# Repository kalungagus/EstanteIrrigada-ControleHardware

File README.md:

# EstanteIrrigada-ControleHardware

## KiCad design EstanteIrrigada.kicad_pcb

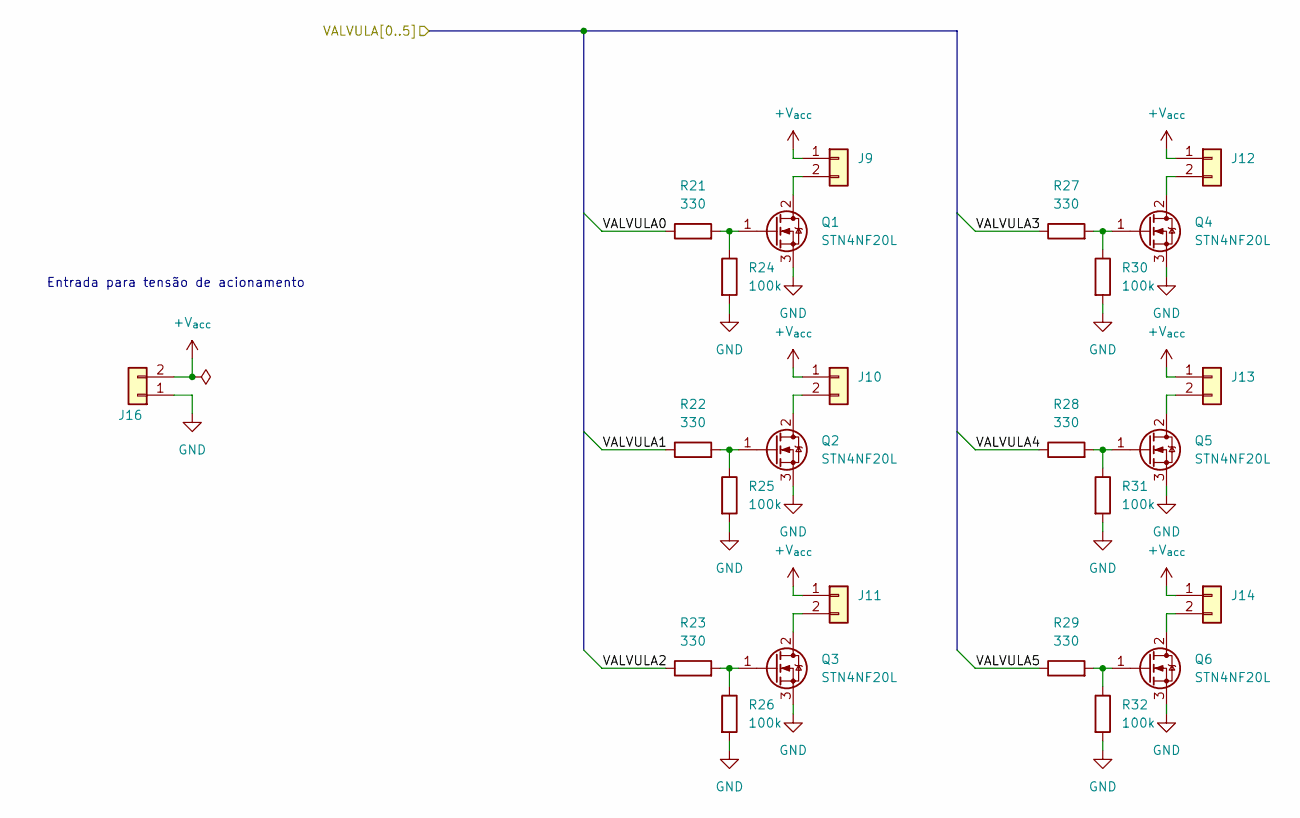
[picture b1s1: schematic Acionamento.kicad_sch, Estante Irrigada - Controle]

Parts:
J9, J10, J11, J12, J13, J14: Conn_01x02; PinHeader_1x02_P2.54mm_Vertical
J16: Conn_01x02; TerminalBlock_bornier-2_P5.08mm
Q1, Q2, Q3, Q4, Q5, Q6: STN4NF20L; SOT-223-3_TabPin2
R21, R22, R23, R27, R28, R29: 330; R_0805_2012Metric_Pad1.20x1.40mm_HandSolder
R24, R25, R26, R30, R31, R32: 100k; R_0805_2012Metric_Pad1.20x1.40mm_HandSolder

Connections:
+V_{acc}: J9.1, J10.1, J11.1, J12.1, J13.1, J14.1, J16.2
/Acionamento/VALVULA0: R21.1; also elsewhere on the board
/Acionamento/VALVULA1: R22.1; also elsewhere on the board
/Acionamento/VALVULA2: R23.1; also elsewhere on the board
/Acionamento/VALVULA3: R27.1; also elsewhere on the board
/Acionamento/VALVULA4: R28.1; also elsewhere on the board
/Acionamento/VALVULA5: R29.1; also elsewhere on the board
GND: J16.1, Q1.3 (S), Q2.3 (S), Q3.3 (S), Q4.3 (S), Q5.3 (S), Q6.3 (S), R24.2, R25.2, R26.2, R30.2, R31.2, R32.2; also elsewhere on the board
unnamed: J9.2, Q1.2 (D)
unnamed: J10.2, Q2.2 (D)
unnamed: J11.2, Q3.2 (D)
unnamed: J12.2, Q4.2 (D)
unnamed: J13.2, Q5.2 (D)
unnamed: J14.2, Q6.2 (D)
unnamed: Q1.1 (G), R21.2, R24.1
unnamed: Q2.1 (G), R22.2, R25.1
unnamed: Q3.1 (G), R23.2, R26.1
unnamed: Q4.1 (G), R27.2, R30.1
unnamed: Q5.1 (G), R28.2, R31.1
unnamed: Q6.1 (G), R29.2, R32.1

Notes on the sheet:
Entrada para tensão de acionamento

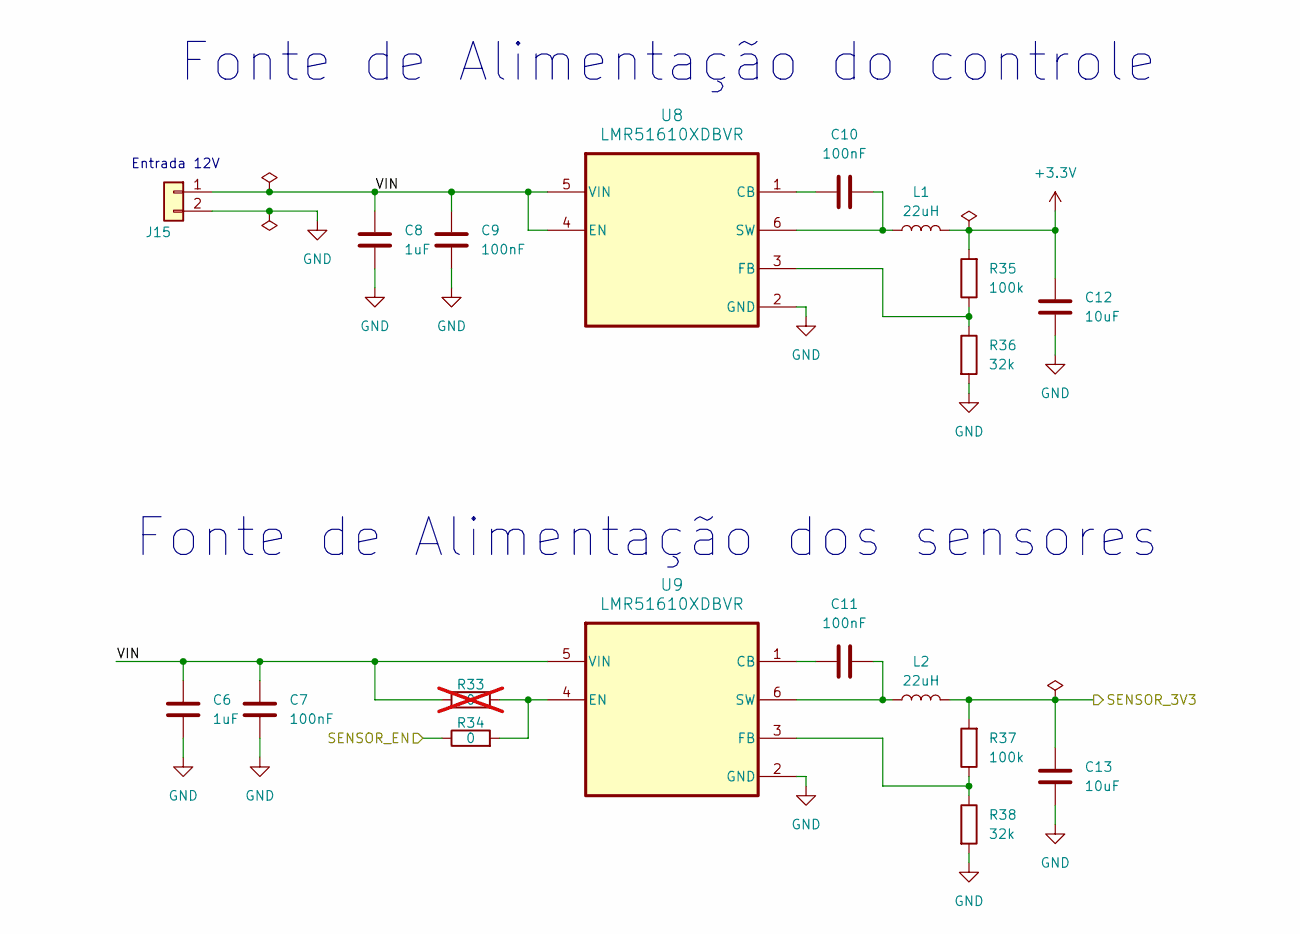
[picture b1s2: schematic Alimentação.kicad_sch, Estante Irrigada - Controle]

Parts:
C6, C8: 1uF; C_0805_2012Metric_Pad1.18x1.45mm_HandSolder
C7, C9, C10, C11: 100nF; C_0805_2012Metric_Pad1.18x1.45mm_HandSolder
C12, C13: 10uF; C_0805_2012Metric_Pad1.18x1.45mm_HandSolder
J15: Conn_01x02; TerminalBlock_bornier-2_P5.08mm
L1, L2: 22uH; L_7.3x7.3_H3.5
R33: 0; R_0805_2012Metric_Pad1.20x1.40mm_HandSolder; not fitted
R34: 0; R_0805_2012Metric_Pad1.20x1.40mm_HandSolder
R35, R37: 100k; R_0805_2012Metric_Pad1.20x1.40mm_HandSolder
R36, R38: 32k; R_0805_2012Metric_Pad1.20x1.40mm_HandSolder
U8, U9: LMR51610XDBVR; DBV0006A-IPC_A

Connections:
+3.3V: C12.1, L1.2, R35.2; also elsewhere on the board
/Alimentação/SENSOR_3V3: C13.1, L2.2, R37.2; also elsewhere on the board
/Alimentação/SENSOR_EN: R34.1; also elsewhere on the board
/Alimentação/VIN: C6.1, C7.1, C8.1, C9.1, J15.1, R33.1, U8.4 (EN), U8.5 (VIN), U9.5 (VIN)
GND: C6.2, C7.2, C8.2, C9.2, C12.2, C13.2, J15.2, R36.2, R38.2, U8.2 (GND), U9.2 (GND); also elsewhere on the board
unnamed: C10.1, U8.1 (CB)
unnamed: R35.1, R36.1, U8.3 (FB)
unnamed: C10.2, L1.1, U8.6 (SW)
unnamed: C11.1, U9.1 (CB)
unnamed: R33.2, R34.2, U9.4 (EN)
unnamed: R37.1, R38.1, U9.3 (FB)
unnamed: C11.2, L2.1, U9.6 (SW)

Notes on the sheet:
Entrada 12V
Fonte de Alimentação dos sensores
Fonte de Alimentação do controle

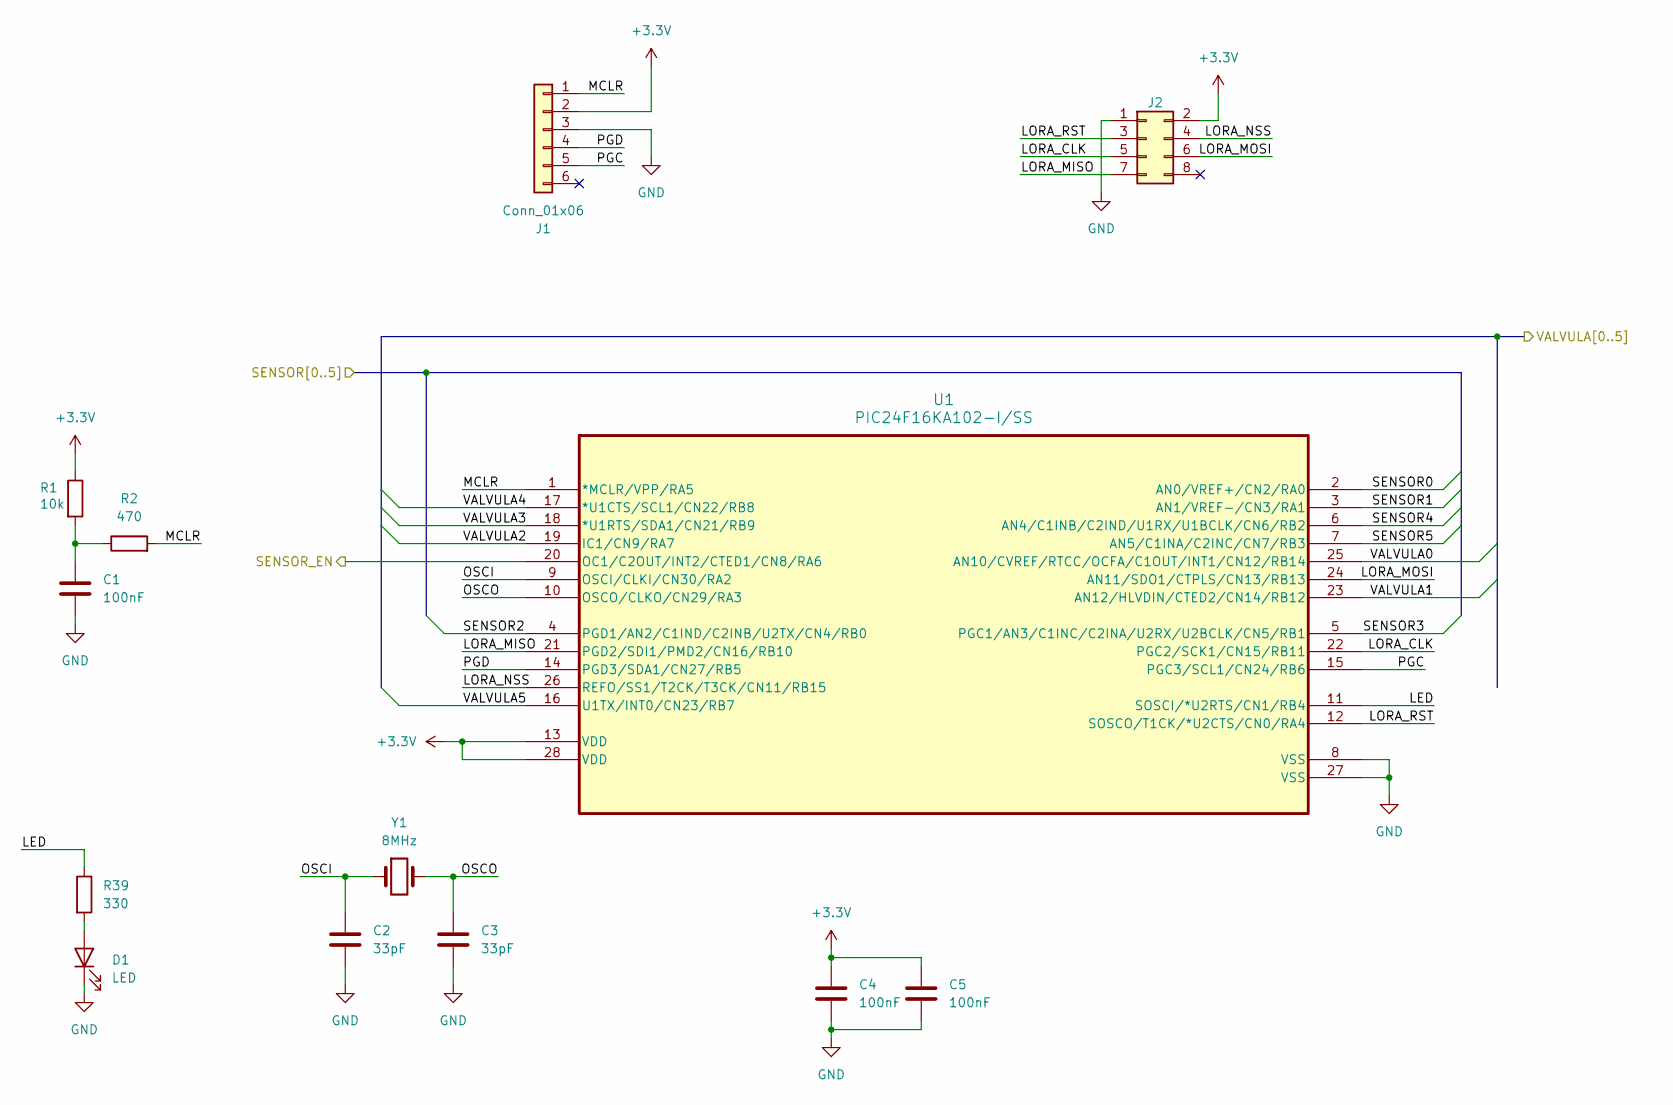
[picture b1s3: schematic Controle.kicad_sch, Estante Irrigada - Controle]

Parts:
C1, C4, C5: 100nF; C_0805_2012Metric_Pad1.18x1.45mm_HandSolder
C2, C3: 33pF; C_0805_2012Metric_Pad1.18x1.45mm_HandSolder
D1: LED; LED_0805_2012Metric_Pad1.15x1.40mm_HandSolder
J1: Conn_01x06; PinHeader_1x06_P2.54mm_Vertical
J2: Conn_02x04_Odd_Even; PinHeader_2x04_P2.54mm_Vertical
R1: 10k; R_0805_2012Metric_Pad1.20x1.40mm_HandSolder
R2: 470; R_0805_2012Metric_Pad1.20x1.40mm_HandSolder
R39: 330; R_0805_2012Metric_Pad1.20x1.40mm_HandSolder
U1: PIC24F16KA102-I/SS; SOP65P780X200-28N
Y1: 8MHz; HC-49&slash_US_11P4X3P8_IQD

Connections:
+3.3V: C4.1, C5.1, J1.2, J2.2, R1.1, U1.13 (VDD), U1.28 (VDD); also elsewhere on the board
/Acionamento/VALVULA0: U1.25 (AN10/CVREF/RTCC/OCFA/C1OUT/INT1/CN12/RB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); also elsewhere on the board
/Acionamento/VALVULA1: U1.23 (AN12/HLVDIN/CTED2/CN14/RB12); also elsewhere on the board
/Acionamento/VALVULA2: U1.19 (IC1/CN9/RA7); also elsewhere on the board
/Acionamento/VALVULA3: U1.18 (*U1RTS/SDA1/CN21/RB9); also elsewhere on the board
/Acionamento/VALVULA4: U1.17 (*U1CTS/SCL1/CN22/RB8); also elsewhere on the board
/Acionamento/VALVULA5: U1.16 (U1TX/INT0/CN23/RB7); also elsewhere on the board
/Alimentação/SENSOR_EN: U1.20 (OC1/C2OUT/INT2/CTED1/CN8/RA6); also elsewhere on the board
/Controle/LED: R39.1, U1.11 (SOSCI/*U2RTS/CN1/RB4)
/Controle/LORA_CLK: J2.5, U1.22 (PGC2/SCK1/CN15/RB11)
/Controle/LORA_MISO: J2.7, U1.21 (PGD2/SDI1/PMD2/CN16/RB10)
/Controle/LORA_MOSI: J2.6, U1.24 (AN11/SDO1/CTPLS/CN13/RB13)
/Controle/LORA_NSS: J2.4, U1.26 (REFO/SS1/T2CK/T3CK/CN11/RB15)
/Controle/LORA_RST: J2.3, U1.12 (SOSCO/T1CK/*U2CTS/CN0/RA4)
/Controle/MCLR: J1.1, R2.2, U1.1 (*MCLR/VPP/RA5)
/Controle/OSCI: C2.1, U1.9 (OSCI/CLKI/CN30/RA2), Y1.1
/Controle/OSCO: C3.1, U1.10 (OSCO/CLKO/CN29/RA3), Y1.2
/Controle/PGC: J1.5, U1.15 (PGC3/SCL1/CN24/RB6)
/Controle/PGD: J1.4, U1.14 (PGD3/SDA1/CN27/RB5)
/Controle/SENSOR0: U1.2 (AN0/VREF+/CN2/RA0); also elsewhere on the board
/Controle/SENSOR1: U1.3 (AN1/VREF-/CN3/RA1); also elsewhere on the board
/Controle/SENSOR2: U1.4 (PGD1/AN2/C1IND/C2INB/U2TX/CN4/RB0); also elsewhere on the board
/Controle/SENSOR3: U1.5 (PGC1/AN3/C1INC/C2INA/U2RX/U2BCLK/CN5/RB1); also elsewhere on the board
/Controle/SENSOR4: U1.6 (AN4/C1INB/C2IND/U1RX/U1BCLK/CN6/RB2); also elsewhere on the board
/Controle/SENSOR5: U1.7 (AN5/C1INA/C2INC/CN7/RB3); also elsewhere on the board
GND: C1.2, C2.2, C3.2, C4.2, C5.2, D1.1 (K), J1.3, J2.1, U1.8 (VSS), U1.27 (VSS); also elsewhere on the board
unnamed: C1.1, R1.2, R2.1
unnamed: D1.2 (A), R39.2

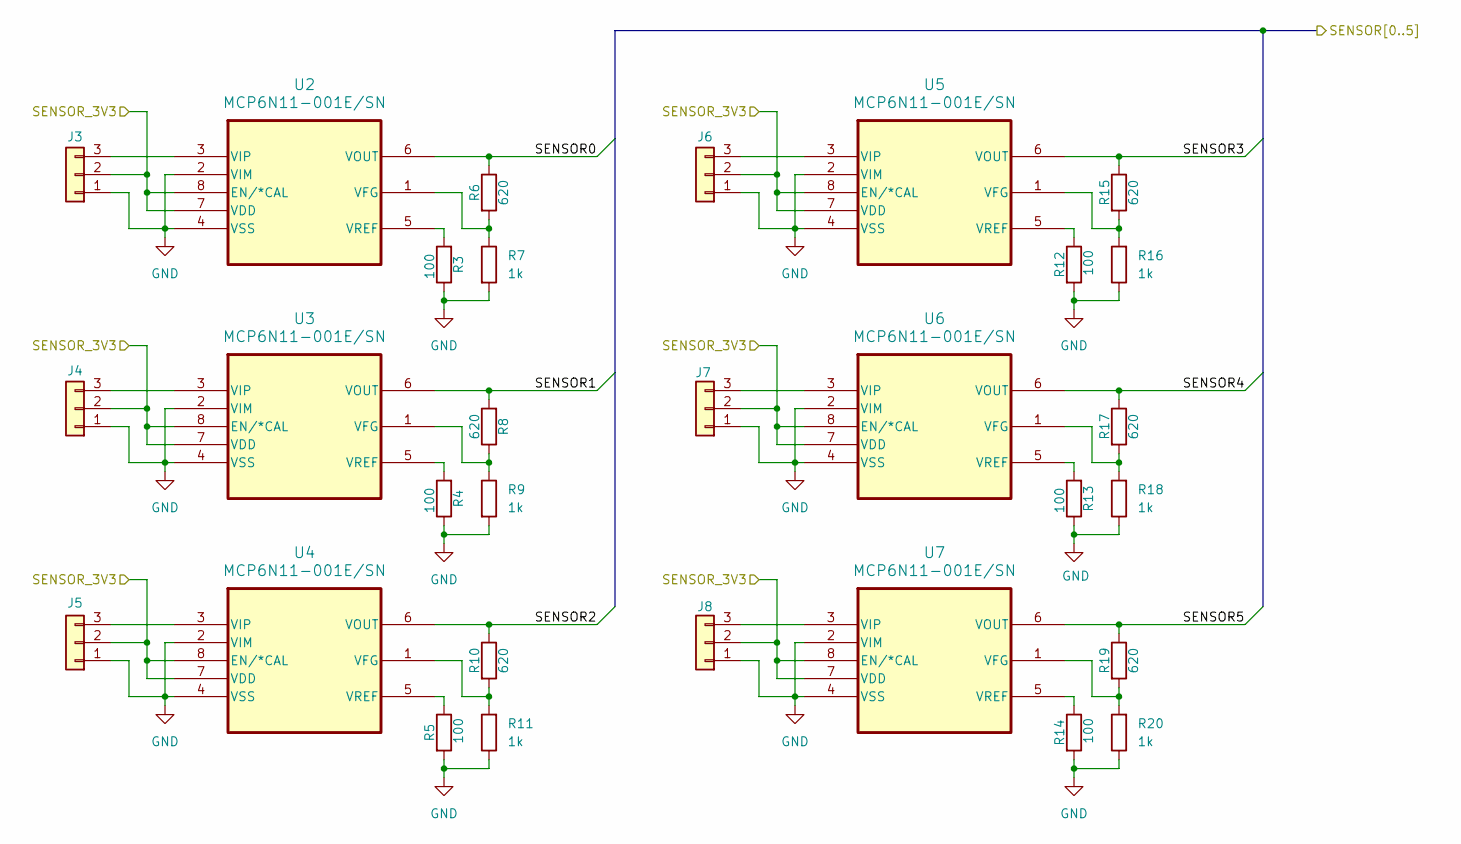
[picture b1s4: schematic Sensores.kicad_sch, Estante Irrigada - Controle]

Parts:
J3, J4, J5, J6, J7, J8: Conn_01x03; PinHeader_1x03_P2.54mm_Vertical
R3, R4, R5, R12, R13, R14: 100; R_0805_2012Metric_Pad1.20x1.40mm_HandSolder
R6, R8, R10, R15, R17, R19: 620; R_0805_2012Metric_Pad1.20x1.40mm_HandSolder
R7, R9, R11, R16, R18, R20: 1k; R_0805_2012Metric_Pad1.20x1.40mm_HandSolder
U2, U3, U4, U5, U6, U7: MCP6N11-001E/SN; SOIC8-N_MC_MCH

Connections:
/Alimentação/SENSOR_3V3: J3.2, J4.2, J5.2, J6.2, J7.2, J8.2, U2.7 (VDD), U2.8 (EN/*CAL), U3.7 (VDD), U3.8 (EN/*CAL), U4.7 (VDD), U4.8 (EN/*CAL), U5.7 (VDD), U5.8 (EN/*CAL), U6.7 (VDD), U6.8 (EN/*CAL), U7.7 (VDD), U7.8 (EN/*CAL); also elsewhere on the board
/Controle/SENSOR0: R6.1, U2.6 (VOUT); also elsewhere on the board
/Controle/SENSOR1: R8.2, U3.6 (VOUT); also elsewhere on the board
/Controle/SENSOR2: R10.1, U4.6 (VOUT); also elsewhere on the board
/Controle/SENSOR3: R15.1, U5.6 (VOUT); also elsewhere on the board
/Controle/SENSOR4: R17.1, U6.6 (VOUT); also elsewhere on the board
/Controle/SENSOR5: R19.1, U7.6 (VOUT); also elsewhere on the board
GND: J3.1, J4.1, J5.1, J6.1, J7.1, J8.1, R3.1, R4.1, R5.2, R7.2, R9.2, R11.1, R12.2, R13.1, R14.2, R16.1, R18.1, R20.1, U2.2 (VIM), U2.4 (VSS), U3.2 (VIM), U3.4 (VSS), U4.2 (VIM), U4.4 (VSS), U5.2 (VIM), U5.4 (VSS), U6.2 (VIM), U6.4 (VSS), U7.2 (VIM), U7.4 (VSS); also elsewhere on the board
unnamed: J3.3, U2.3 (VIP)
unnamed: J4.3, U3.3 (VIP)
unnamed: J5.3, U4.3 (VIP)
unnamed: J6.3, U5.3 (VIP)
unnamed: J7.3, U6.3 (VIP)
unnamed: J8.3, U7.3 (VIP)
unnamed: R6.2, R7.1, U2.1 (VFG)
unnamed: R3.2, U2.5 (VREF)
unnamed: R8.1, R9.1, U3.1 (VFG)
unnamed: R4.2, U3.5 (VREF)
unnamed: R10.2, R11.2, U4.1 (VFG)
unnamed: R5.1, U4.5 (VREF)
unnamed: R15.2, R16.2, U5.1 (VFG)
unnamed: R12.1, U5.5 (VREF)
unnamed: R17.2, R18.2, U6.1 (VFG)
unnamed: R13.2, U6.5 (VREF)
unnamed: R19.2, R20.2, U7.1 (VFG)
unnamed: R14.1, U7.5 (VREF)

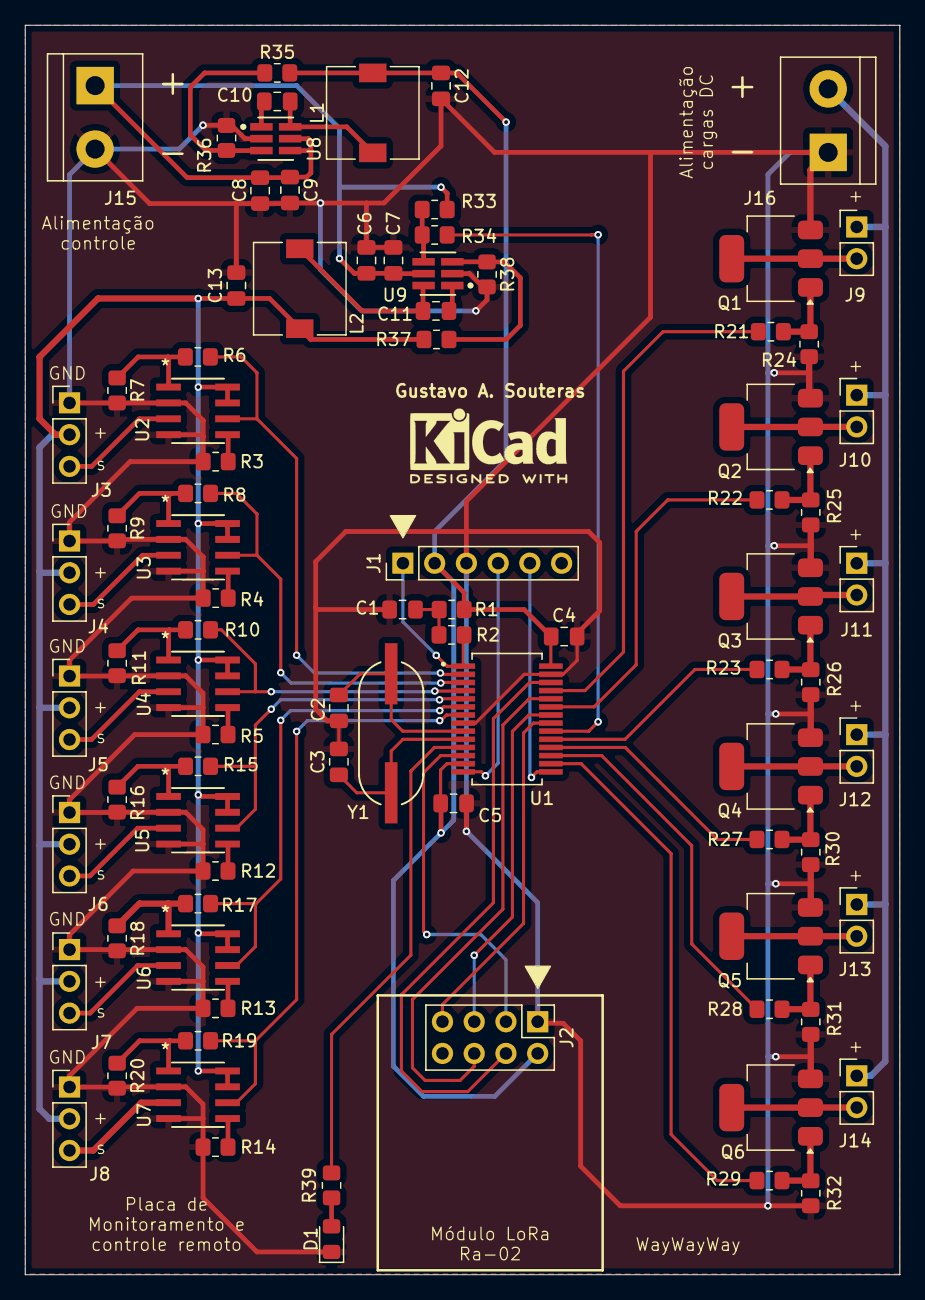
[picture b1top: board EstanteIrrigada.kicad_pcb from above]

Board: 2 copper layers, 70.0 x 100.0 mm, 87 parts (0 on the bottom side), 68 nets.

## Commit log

2024-08-08 First commit of this project. Created schematics and PCB for controlling 6 microvalves and 6 soil humidity sensors, used to irrigate up to 6 vases. Intended to be controlled remotely by LoRa Network.
